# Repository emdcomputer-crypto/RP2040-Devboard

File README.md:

# RP2040 Devboard

This is my custom RP2040 devboard for Hack Club Half Life week 5. I followed the guided devboard project and made my schematic and PCB in KiCad. The board has USB-C, an RP2040, flash memory, a 12 MHz crystal, an LDO and headers to get to the GPIO pins.

## How it works

The RP2040 is the main chip on the board. It uses external flash memory to store the program and a 12 MHz crystal for its clock. USB-C brings power and the USB data connections onto the board. The LDO regulates the power for the 3.3V parts, and the headers bring the GPIO pins out so they can be used for other things.

## How I made it

i started by following the guide and building the schematic in KiCad. There was a lot of wiring to do for the USB-C, flash memory, crystal and all the GPIO headers. I also had to check the RP2040 datasheet and make sure the parts and footprints were right.

The PCB was the hardest part for me because there wasnt much space and the traces kept getting in the way of each other. I moved things around a lot and added vias to get the connections onto both layers. After routing I worked through the DRC errors one by one, cleaned up the silkscreen and exported the files for JLCPCB.

## Bill of materials

The full parts list is in the picture above but you don't need to copy it as i placed all of them in the BOM file for jlcpcb. My JLCPCB estimate was:

| Item | Cost |
| --- | ---: |
| Production and assembly | $58.28 |
| Estimated shipping and tax | $55.89 |
| Total | $114.17 |

## Project files

- [Hardware](Hardware/) - KiCad schematic, PCB layout and project files
- [FabricationFiles](FabricationFiles/) - files exported for PCB manufacturing
- [BOM.csv](BOM.csv) - project cost and parts list
- [JOURNAL.md](JOURNAL.md) - my work notes while making the board

## Guide

I followed the [Hack Club Blueprint RP2040 Devboard guide](https://blueprint.hackclub.com/starter-projects/devboard).

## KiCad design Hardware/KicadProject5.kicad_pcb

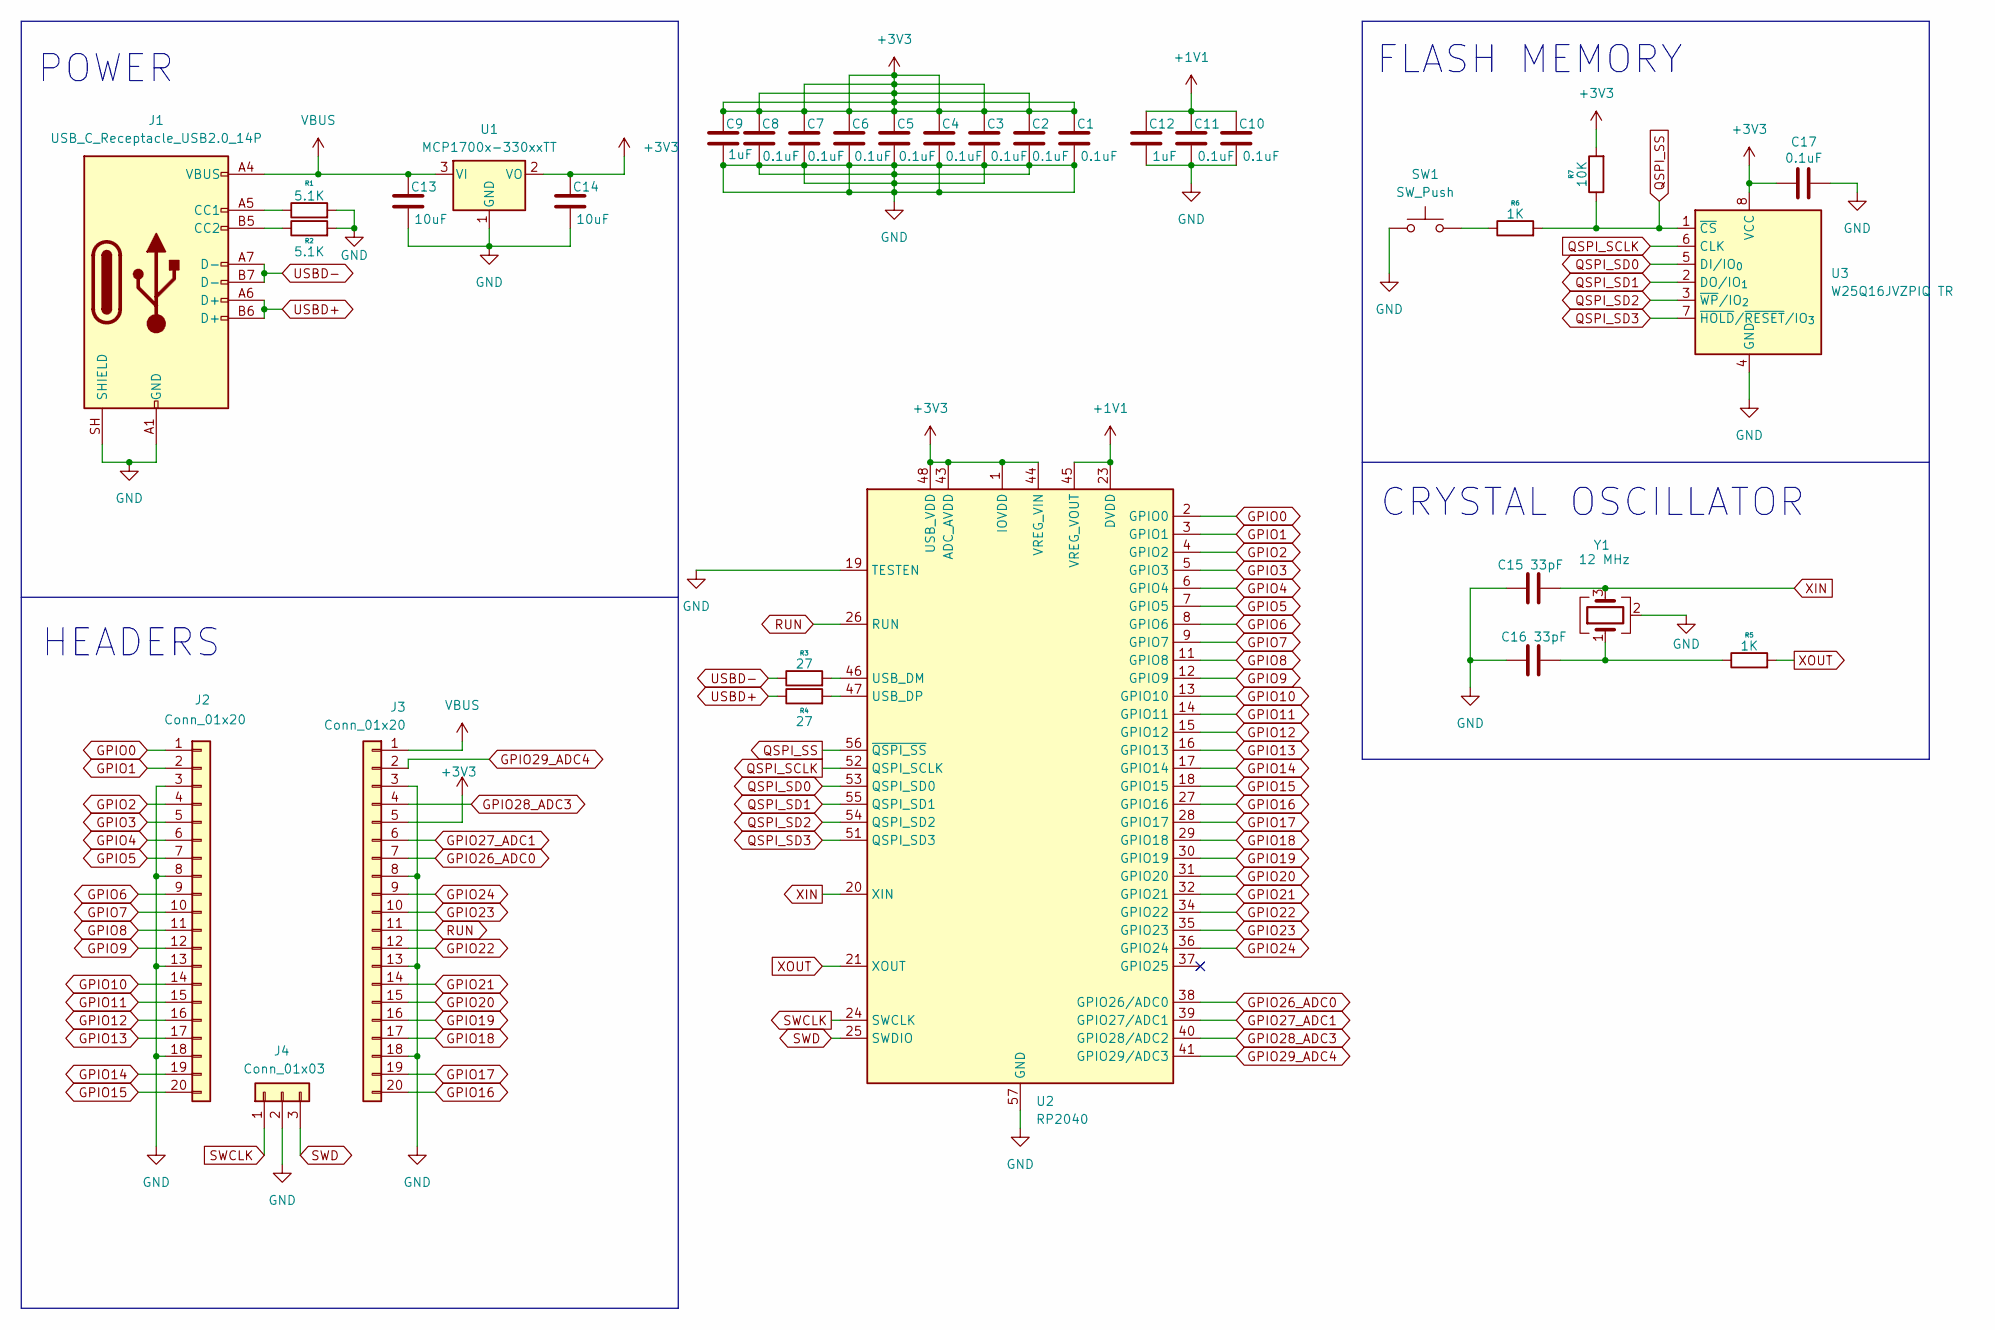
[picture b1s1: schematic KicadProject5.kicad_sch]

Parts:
C1, C2, C3, C4, C5, C6, C7, C8, C10, C11, C17: 0.1uF; C_0402_1005Metric
C9, C12: 1uF; C_0402_1005Metric
C13, C14: 10uF; C_0603_1608Metric
C15, C16: 33pF; C_0402_1005Metric
J1: USB_C_Receptacle_USB2.0_14P; USB_C_Receptacle_HRO_TYPE-C-31-M-12
J2, J3: Conn_01x20; PinHeader_1x20_P2.54mm_Vertical
J4: Conn_01x03; PinHeader_1x03_P2.54mm_Vertical
R1, R2: 5.1K; R_0402_1005Metric
R3, R4: 27; R_0402_1005Metric
R5, R6: 1K; R_0402_1005Metric
R7: 10K; R_0402_1005Metric
SW1: SW_Push; SW_Push_SPST_NO_Alps_SKRK
U1: MCP1700x-330xxTT; SOT-23
U2: RP2040; QFN-56-1EP_7x7mm_P0.4mm_EP3.2x3.2mm
U3: W25Q16JVZPIQ TR; Winbond_USON-8-1EP_3x2mm_P0.5mm_EP0.2x1.6mm
Y1: 12 MHz; Crystal_SMD_3225-4Pin_3.2x2.5mm

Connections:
+1V1: C10.1, C11.1, C12.1, U2.23 (DVDD), U2.45 (VREG_VOUT), U2.50 (DVDD)
+3V3: C1.1, C2.1, C3.1, C4.1, C5.1, C6.1, C7.1, C8.1, C9.1, C14.1, C17.1, J3.5, R7.2, U1.2 (VO), U2.1 (IOVDD), U2.10 (IOVDD), U2.22 (IOVDD), U2.33 (IOVDD), U2.42 (IOVDD), U2.43 (ADC_AVDD), U2.44 (VREG_VIN), U2.48 (USB_VDD), U2.49 (IOVDD), U3.8 (VCC)
GND: C1.2, C2.2, C3.2, C4.2, C5.2, C6.2, C7.2, C8.2, C9.2, C10.2, C11.2, C12.2, C13.2, C14.2, C15.1, C16.1, C17.2, J1.A1 (GND), J1.A12 (GND), J1.B1 (GND), J1.B12 (GND), J1.SH (SHIELD), J2.3, J2.8, J2.13, J2.18, J3.3, J3.8, J3.13, J3.18, J4.2, R1.2, R2.2, SW1.1, U1.1 (GND), U2.19 (TESTEN), U2.57 (GND), U3.4 (GND), Y1.2 (G), Y1.4 (G)
GPIO0: J2.1, U2.2 (GPIO0)
GPIO1: J2.2, U2.3 (GPIO1)
GPIO2: J2.4, U2.4 (GPIO2)
GPIO3: J2.5, U2.5 (GPIO3)
GPIO4: J2.6, U2.6 (GPIO4)
GPIO5: J2.7, U2.7 (GPIO5)
GPIO6: J2.9, U2.8 (GPIO6)
GPIO7: J2.10, U2.9 (GPIO7)
GPIO8: J2.11, U2.11 (GPIO8)
GPIO9: J2.12, U2.12 (GPIO9)
GPIO10: J2.14, U2.13 (GPIO10)
GPIO11: J2.15, U2.14 (GPIO11)
GPIO12: J2.16, U2.15 (GPIO12)
GPIO13: J2.17, U2.16 (GPIO13)
GPIO14: J2.19, U2.17 (GPIO14)
GPIO15: J2.20, U2.18 (GPIO15)
GPIO16: J3.20, U2.27 (GPIO16)
GPIO17: J3.19, U2.28 (GPIO17)
GPIO18: J3.17, U2.29 (GPIO18)
GPIO19: J3.16, U2.30 (GPIO19)
GPIO20: J3.15, U2.31 (GPIO20)
GPIO21: J3.14, U2.32 (GPIO21)
GPIO22: J3.12, U2.34 (GPIO22)
GPIO23: J3.10, U2.35 (GPIO23)
GPIO24: J3.9, U2.36 (GPIO24)
GPIO26_ADC0: J3.7, U2.38 (GPIO26/ADC0)
GPIO27_ADC1: J3.6, U2.39 (GPIO27/ADC1)
GPIO28_ADC3: J3.4, U2.40 (GPIO28/ADC2)
GPIO29_ADC4: J3.2, U2.41 (GPIO29/ADC3)
unnamed: C16.2, R5.1, Y1.1
unnamed: J1.A5 (CC1), R1.1
unnamed: J1.B5 (CC2), R2.1
unnamed: R6.1, SW1.2
unnamed: R3.2, U2.46 (USB_DM)
unnamed: R4.2, U2.47 (USB_DP)
QSPI_SCLK: U2.52 (QSPI_SCLK), U3.6 (CLK)
QSPI_SD0: U2.53 (QSPI_SD0), U3.5 (DI/IO_{0})
QSPI_SD1: U2.55 (QSPI_SD1), U3.2 (DO/IO_{1})
QSPI_SD2: U2.54 (QSPI_SD2), U3.3 (~WP/IO_{2})
QSPI_SD3: U2.51 (QSPI_SD3), U3.7 (~HOLD/~RESET/IO_{3})
QSPI_SS: R6.2, R7.1, U2.56 (~QSPI_SS), U3.1 (~CS)
RUN: J3.11, U2.26 (RUN)
SWCLK: J4.1, U2.24 (SWCLK)
SWD: J4.3, U2.25 (SWDIO)
USBD+: J1.A6 (D+), J1.B6 (D+), R4.1
USBD-: J1.A7 (D-), J1.B7 (D-), R3.1
VBUS: C13.1, J1.A4 (VBUS), J1.A9 (VBUS), J1.B4 (VBUS), J1.B9 (VBUS), J3.1, U1.3 (VI)
XIN: C15.2, U2.20 (XIN), Y1.3
XOUT: R5.2, U2.21 (XOUT)

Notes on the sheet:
HEADERS
POWER
CRYSTAL OSCILLATOR
FLASH MEMORY

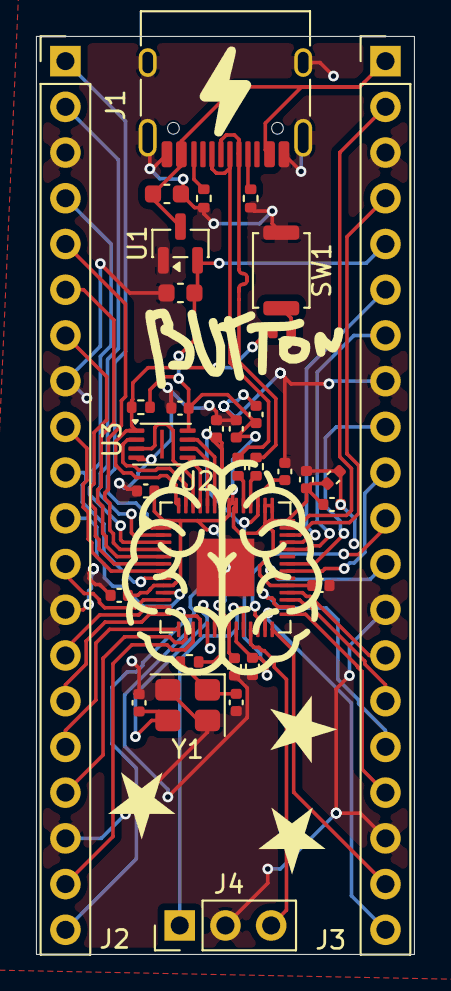
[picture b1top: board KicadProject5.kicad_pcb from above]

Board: 2 copper layers, 21.0 x 51.0 mm, 33 parts (0 on the bottom side), 52 nets.

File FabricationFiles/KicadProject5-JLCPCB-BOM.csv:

"Top Designator","Bottom Designator","Comment","Footprint","JLCPCB Part #"
"C1,C2,C3,C4,C5,C6,C7,C8,C10,C11,C17","","0.1uF","C_0402_1005Metric","C1525"
"C9,C12","","1uF","C_0402_1005Metric","C52923"
"C13,C14","","10uF","C_0603_1608Metric","C19702"
"C15,C16","","33pF","C_0402_1005Metric","C1562"
"J1","","USB_C_Receptacle_USB2.0_14P","USB_C_Receptacle_HRO_TYPE-C-31-M-12","C165948"
"R1,R2","","5.1K","R_0402_1005Metric","C25905"
"R3,R4","","27","R_0402_1005Metric","C25100"
"R5,R6","","1K","R_0402_1005Metric","C11702"
"R7","","10K","R_0402_1005Metric","C25744"
"SW1","","SW_Push","SW_Push_SPST_NO_Alps_SKRK","C720477"
"U1","","MCP1700x-330xxTT","SOT-23","C39051"
"U2","","RP2040","QFN-56-1EP_7x7mm_P0.4mm_EP3.2x3.2mm","C2040"
"U3","","W25Q16JVUXIQ TR","Winbond_USON-8-1EP_3x2mm_P0.5mm_EP0.2x1.6mm","C2843335"
"Y1","","12MHz","Crystal_SMD_3225-4Pin_3.2x2.5mm","C9002"
